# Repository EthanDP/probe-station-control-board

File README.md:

# Semiconductor Probe Station Control Board
Schematics, libraries, and a layout for a relay control board used to interface an NI PCIe card with a chip probing station.

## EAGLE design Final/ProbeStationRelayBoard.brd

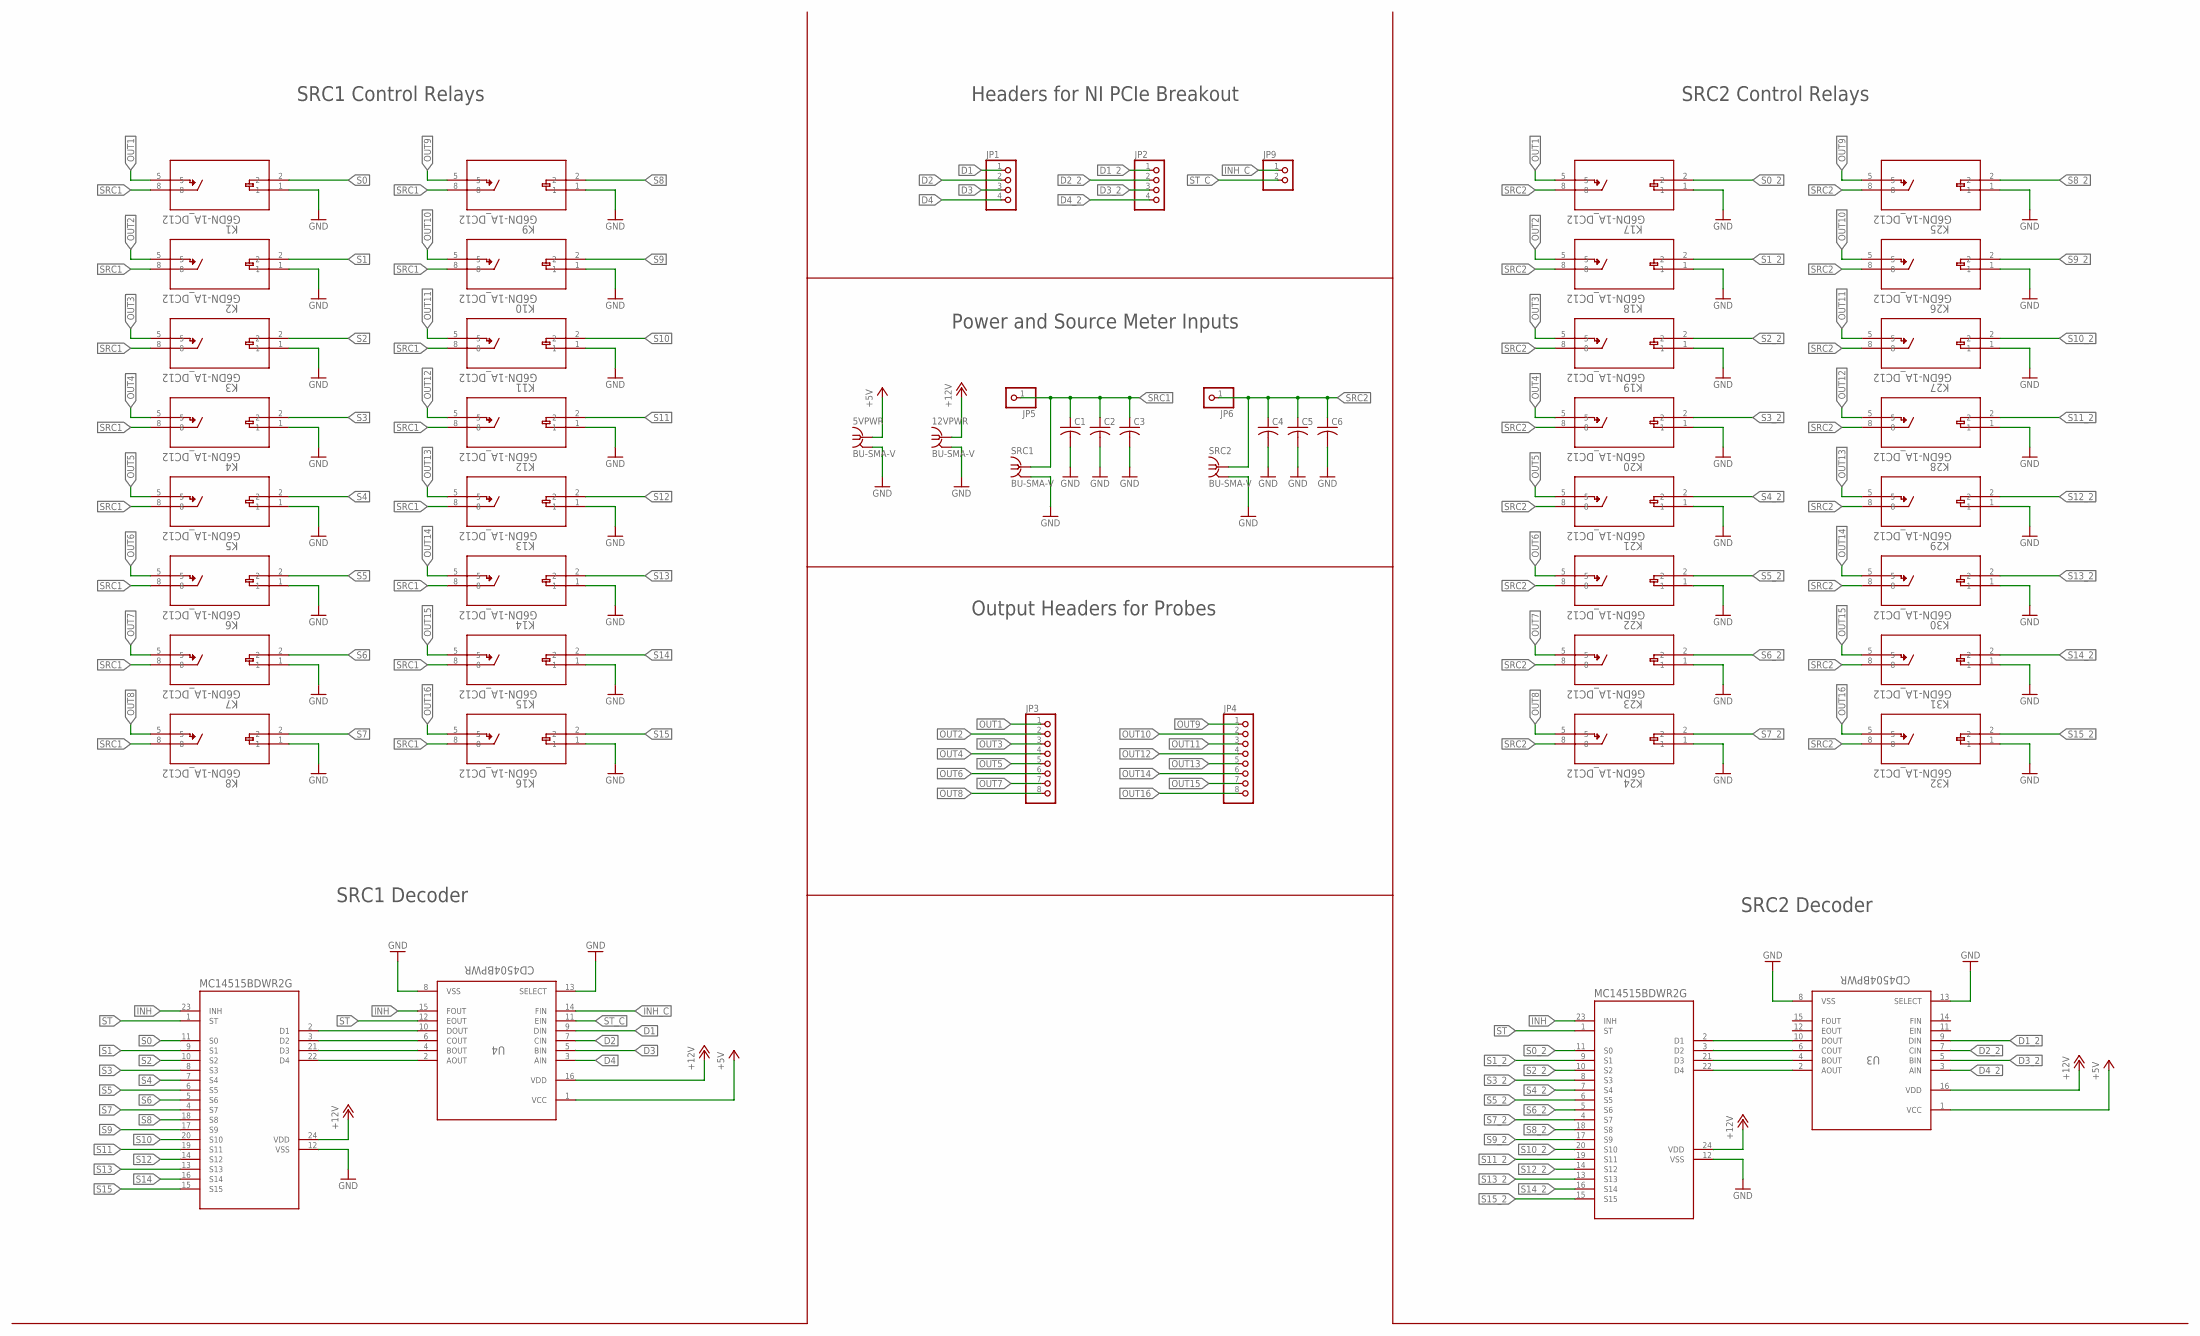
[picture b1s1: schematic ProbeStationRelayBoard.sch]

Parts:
5VPWR, 12VPWR: BU-SMA-V
C1, C2, C3, C4, C5, C6: C-USC0805; C0805
JP1, JP2: PINHD-1X4; 1X04
JP3, JP4: PINHD-1X8; 1X08
JP5, JP6: PINHD-1X1; 1X01
JP9: PINHD-1X2; 1X02
K1, K2, K3, K4, K5, K6, K7, K8, K9, K10, K11, K12, K13, K14, K15, K16, K17, K18, K19, K20, K21, K22, K23, K24, K25, K26, K27, K28, K29, K30, K31, K32: G6DN-1A_DC12; RELAY_G6DN-1A_OMR
SRC1, SRC2: BU-SMA-V
U1, U2: MC14515BDWR2G; SOIC-24WB_ONS
U3, U4: CD4504BPWR; PW0016A_N

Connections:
+5V: 5VPWR.1, U3.1 (VCC), U4.1 (VCC)
+12V: 12VPWR.1, U1.24 (VDD), U2.24 (VDD), U3.16 (VDD), U4.16 (VDD)
D1: JP1.1, U4.9 (DIN)
D1_2: JP2.1, U3.9 (DIN)
D2: JP1.2, U4.7 (CIN)
D2_2: JP2.2, U3.7 (CIN)
D3: JP1.3, U4.5 (BIN)
D3_2: JP2.3, U3.5 (BIN)
D4: JP1.4, U4.3 (AIN)
D4_2: JP2.4, U3.3 (AIN)
GND: 5VPWR.2, 5VPWR.3 (2), 5VPWR.4 (2), 5VPWR.5 (2), 12VPWR.2, 12VPWR.3 (2), 12VPWR.4 (2), 12VPWR.5 (2), C1.2, C2.2, C3.2, C4.2, C5.2, C6.2, K1.1, K2.1, K3.1, K4.1, K5.1, K6.1, K7.1, K8.1, K9.1, K10.1, K11.1, K12.1, K13.1, K14.1, K15.1, K16.1, K17.1, K18.1, K19.1, K20.1, K21.1, K22.1, K23.1, K24.1, K25.1, K26.1, K27.1, K28.1, K29.1, K30.1, K31.1, K32.1, SRC1.2, SRC1.3 (2), SRC1.4 (2), SRC1.5 (2), SRC2.2, SRC2.3 (2), SRC2.4 (2), SRC2.5 (2), U1.12 (VSS), U2.12 (VSS), U3.8 (VSS), U3.13 (SELECT), U4.8 (VSS), U4.13 (SELECT)
INH: U1.23 (INH), U2.23 (INH), U4.15 (FOUT)
INH_C: JP9.1, U4.14 (FIN)
unnamed: U2.22 (D4), U4.2 (AOUT)
unnamed: U2.21 (D3), U4.4 (BOUT)
unnamed: U2.3 (D2), U4.6 (COUT)
unnamed: U2.2 (D1), U4.10 (DOUT)
unnamed: U1.22 (D4), U3.2 (AOUT)
unnamed: U1.21 (D3), U3.4 (BOUT)
unnamed: U1.3 (D2), U3.6 (COUT)
unnamed: U1.2 (D1), U3.10 (DOUT)
OUT1: JP3.1, K1.5, K17.5
OUT2: JP3.2, K2.5, K18.5
OUT3: JP3.3, K3.5, K19.5
OUT4: JP3.4, K4.5, K20.5
OUT5: JP3.5, K5.5, K21.5
OUT6: JP3.6, K6.5, K22.5
OUT7: JP3.7, K7.5, K23.5
OUT8: JP3.8, K8.5, K24.5
OUT9: JP4.1, K9.5, K25.5
OUT10: JP4.2, K10.5, K26.5
OUT11: JP4.3, K11.5, K27.5
OUT12: JP4.4, K12.5, K28.5
OUT13: JP4.5, K13.5, K29.5
OUT14: JP4.6, K14.5, K30.5
OUT15: JP4.7, K15.5, K31.5
OUT16: JP4.8, K16.5, K32.5
S0: K1.2, U2.11 (S0)
S0_2: K17.2, U1.11 (S0)
S1: K2.2, U2.9 (S1)
S1_2: K18.2, U1.9 (S1)
S2: K3.2, U2.10 (S2)
S2_2: K19.2, U1.10 (S2)
S3: K4.2, U2.8 (S3)
S3_2: K20.2, U1.8 (S3)
S4: K5.2, U2.7 (S4)
S4_2: K21.2, U1.7 (S4)
S5: K6.2, U2.6 (S5)
S5_2: K22.2, U1.6 (S5)
S6: K7.2, U2.5 (S6)
S6_2: K23.2, U1.5 (S6)
S7: K8.2, U2.4 (S7)
S7_2: K24.2, U1.4 (S7)
S8: K9.2, U2.18 (S8)
S8_2: K25.2, U1.18 (S8)
S9: K10.2, U2.17 (S9)
S9_2: K26.2, U1.17 (S9)
S10: K11.2, U2.20 (S10)
S10_2: K27.2, U1.20 (S10)
S11: K12.2, U2.19 (S11)
S11_2: K28.2, U1.19 (S11)
S12: K13.2, U2.14 (S12)
S12_2: K29.2, U1.14 (S12)
S13: K14.2, U2.13 (S13)
S13_2: K30.2, U1.13 (S13)
S14: K15.2, U2.16 (S14)
S14_2: K31.2, U1.16 (S14)
S15: K16.2, U2.15 (S15)
S15_2: K32.2, U1.15 (S15)
SRC1: C1.1, C2.1, C3.1, JP5.1, K1.8, K2.8, K3.8, K4.8, K5.8, K6.8, K7.8, K8.8, K9.8, K10.8, K11.8, K12.8, K13.8, K14.8, K15.8, K16.8, SRC1.1
SRC2: C4.1, C5.1, C6.1, JP6.1, K17.8, K18.8, K19.8, K20.8, K21.8, K22.8, K23.8, K24.8, K25.8, K26.8, K27.8, K28.8, K29.8, K30.8, K31.8, K32.8, SRC2.1
ST: U1.1 (ST), U2.1 (ST), U4.12 (EOUT)
ST_C: JP9.2, U4.11 (EIN)

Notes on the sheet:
SRC1 Decoder
Headers for NI PCIe Breakout
SRC1 Control Relays
SRC2 Control Relays
SRC2 Decoder
Power and Source Meter Inputs
Output Headers for Probes

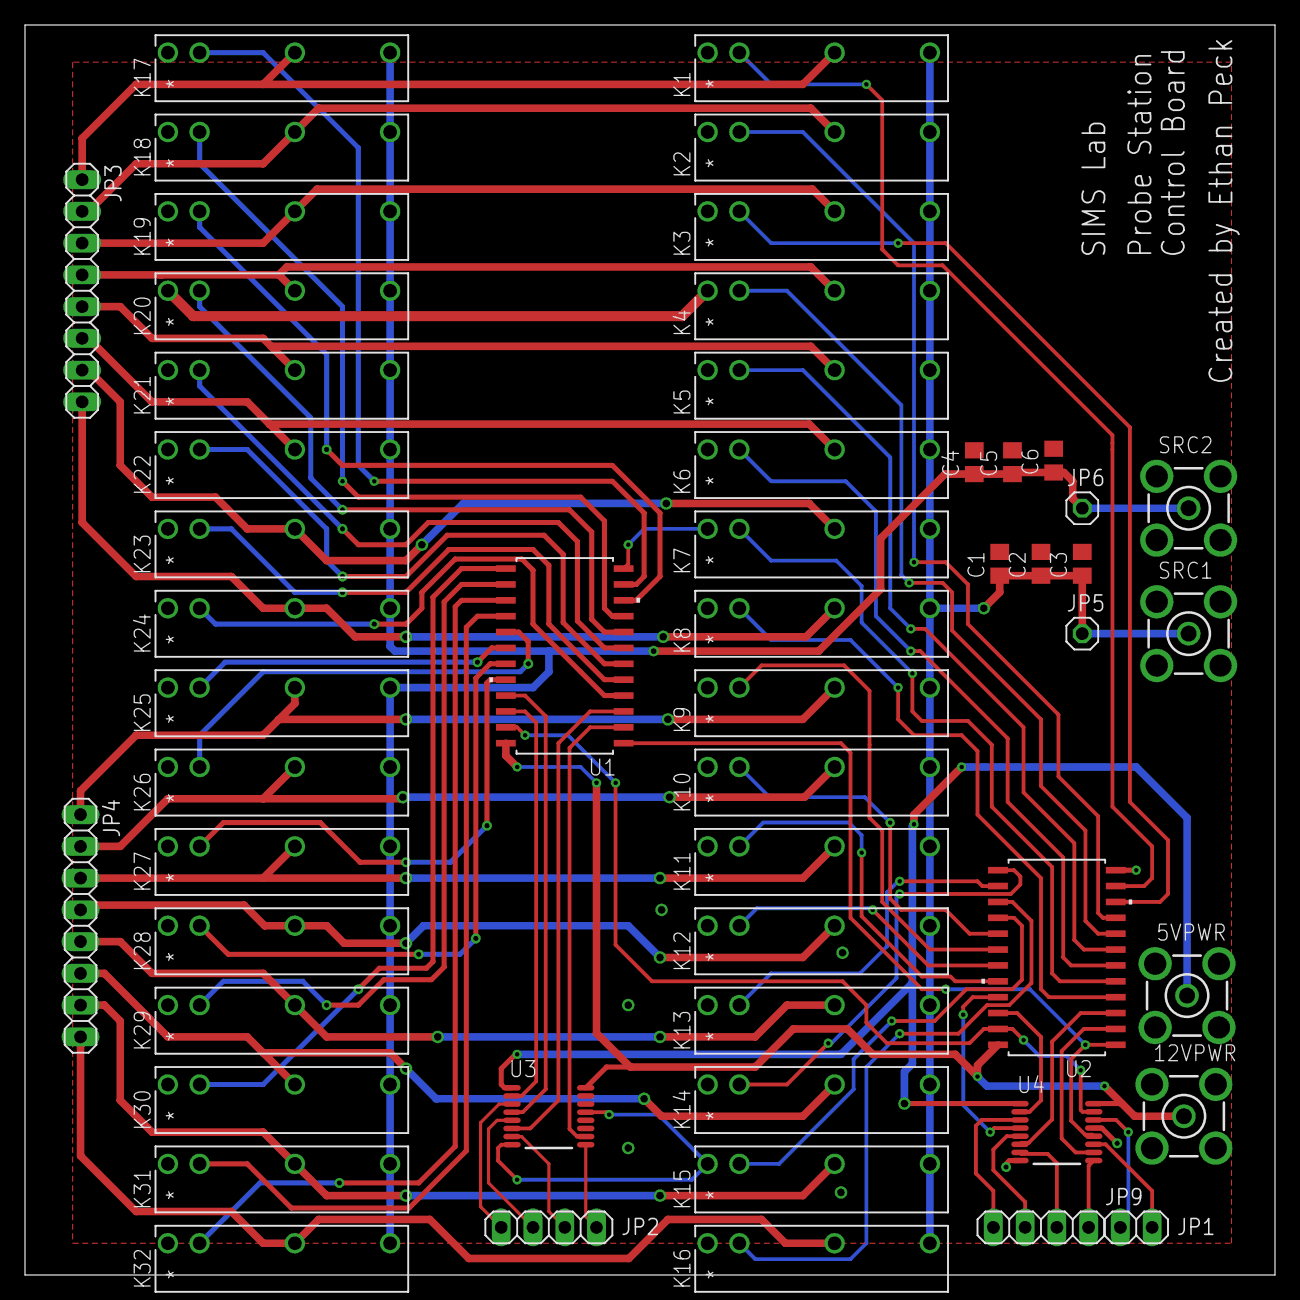
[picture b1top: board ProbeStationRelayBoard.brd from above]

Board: 2 copper layers, 100.0 x 100.0 mm, 53 parts (0 on the bottom side), 73 nets.

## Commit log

2021-11-05 Add schematic, libraries, and schematic screenshot
2021-11-07 Revision 2, folders for revisions, add level shifter, more pins/connectors for power and source meter
2021-11-08 Final schematic, layout, and gerber files
2021-11-09 Revise final layout and schematic

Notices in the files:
parts and their libraries:
COPYRIGHT: Copyright (C) 2021 Ultra Librarian. All rights reserved.
